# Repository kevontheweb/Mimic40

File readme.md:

# Mimic40

A tiny ortho board that is pretending to be a fullsize. 

> I have not ordered any pcbs yet so consider these files *under development* until i can order some to test if they work.

<!--  -->

## tools used to build

1. [KLE](http://www.keyboard-layout-editor.com/##@_name=Mimic40&author=kevontheweb.net&background_name=PBT%20Black&style=background-image%2F:%20url('%2F%2Fbg%2F%2Fplastic%2F%2Fpbt-black.png')%2F%3B&$$hashKey=0BG%3B&radii=10px&switchMount=cherry&switchBrand=gateron&switchType=KS-3-Yellow&pcb:false&plate:true%3B&@_c=%23ffffff&p=DSA&f:4%3B&=Tab&=Q&=W&=E&=R&=T&=Y&=U&=I&=O&=P&=Back%20Space&=Delete&_x:0.5%3B&=1&=2&=3%3B&@_c=%23c7c7c7%3B&=Esc&_c=%23ffffff%3B&=A&=S&=D&_n:true%3B&=F&=G&=H&_n:true%3B&=J&=K&=L&=%2F%3B&='&=Return&_x:0.5%3B&=4&=5&=6%3B&@=Shift&=Z&=X&=C&=V&=B&=N&=M&=,&=.&=%2F%2F&=Shift&_x:1.5%3B&=7&=8&=9%3B&@_y:-0.75&x:12.25&t=%23ffffff%3B&=%2F&uarr%2F%3B%3B&@_y:-0.25&t=%23000000&w:1.25%3B&=Ctrl&_w:1.25%3B&=Alt&_w:1.25%3B&=Super&_t=%23ffffff&w:1.25%3B&=%2F&dArr%2F%3B&_t=%23000000&a:7&w:2%3B&=&_t=%23ffffff&a:4&w:1.25%3B&=%2F&uArr%2F%3B&_t=%23000000&w:1.25%3B&=Alt&_w:1.25%3B&=Fn&_x:3.75%3B&=0&=Enter%3B&@_y:-0.75&x:11.25&t=%23ffffff%3B&=%2F&larr%2F%3B&=%2F&darr%2F%3B&=%2F&rarr%2F)
2. [kicad](https://www.kicad.org/download/) EDA
5. [cherry mx datasheet](https://imgur.com/a/XMoHF)
<!-- x. [keyboard firmware builder](https://builder.mrkeebs.com/) for the matrix (if handwired) -->

These may be helpful for future in the design of a case

1. [builder.swillkb](builder.swillkb.com/) for the case
2. [ai03 plate generator](https://kbplate.ai03.com/)

## screenshots

## references

> this was in part inspired by  [This reddit post](https://www.reddit.com/r/MechanicalKeyboards/comments/ksto32/chocolate_bar/?utm_source=share&utm_medium=web2x&context=3).

# to do

- [x] define outer geometry
- [x] per key rgb
- [x] route rows and columns
- [x] switch to rp2040 based design (no dev board)
- [x] make plate cutout file (remember to add a 2u plate mount stabiliser)
- [ ] design a case (acrlic laser cut or possible 3d printed)
- [ ] order pcbs to test
- [ ] firmware
- [ ] take it from there

## how to order

- upload gerbers
- upload bom and pos files
- confirm placements
- order missing parts elsewhere (F1 and the sockets)

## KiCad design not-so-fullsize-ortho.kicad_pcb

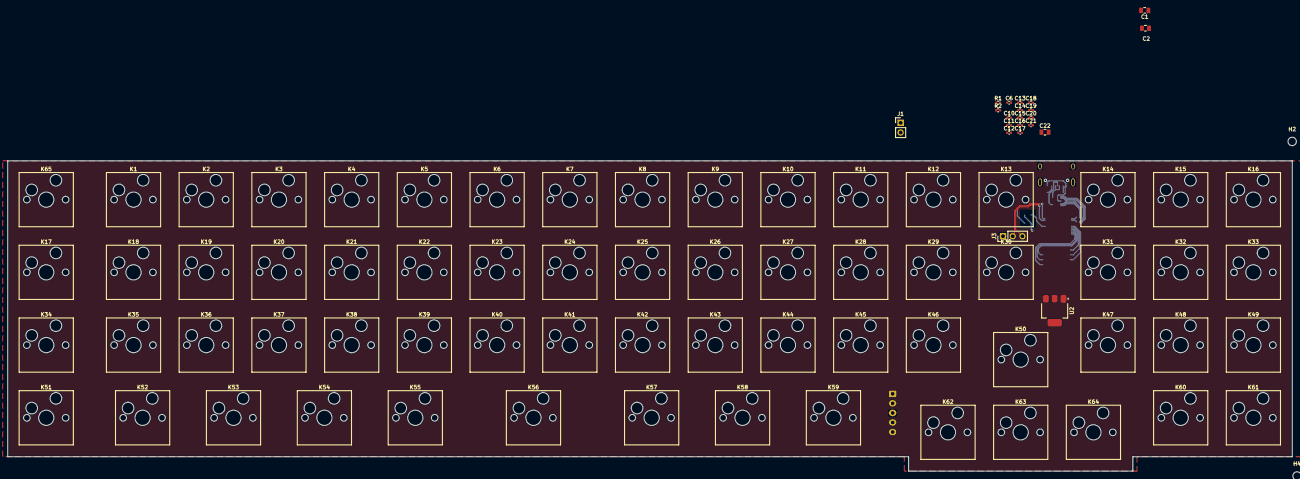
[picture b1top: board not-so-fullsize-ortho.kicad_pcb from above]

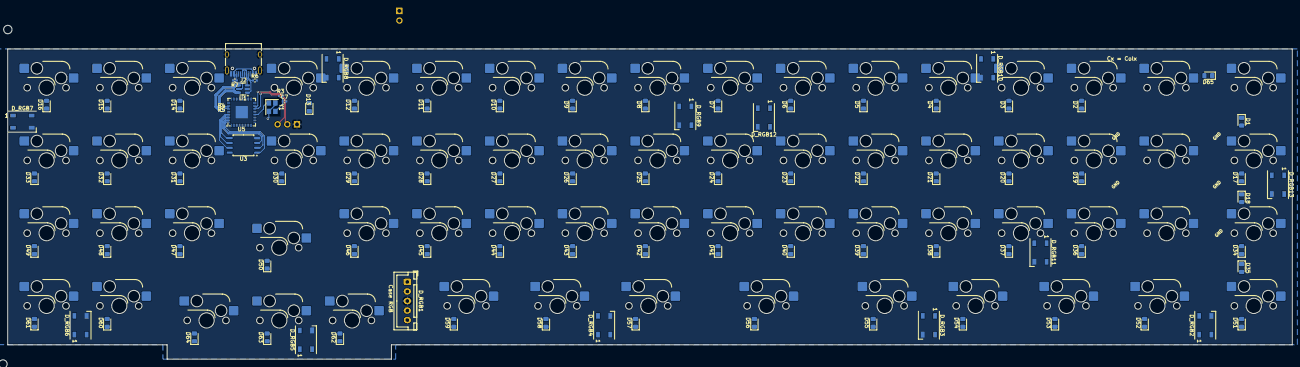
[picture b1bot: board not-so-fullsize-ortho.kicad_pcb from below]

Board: 2 copper layers, 336.5 x 81.2 mm, 179 parts (89 on the bottom side), 122 nets.

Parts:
C1, C2, C22: 10u; C_0805_2012Metric
C6, C7: 15p; C_0402_1005Metric
C10, C11, C12, C14, C16, C17, C18, C19, C20, C21: 100n; C_0402_1005Metric
C13, C15: 1u; C_0402_1005Metric
D1, D2, D3, D4, D5, D6, D7, D8, D9, D10, D11, D12, D13, D14, D15, D16, D17, D18, D19, D20, D21, D22, D23, D24, D25, D26, D27, D28, D29, D30, D31, D32, D33, D34, D35, D36, D37, D38, D39, D40, D41, D42, D43, D44, D45, D46, D47, D48, D49, D50, D51, D52, D53, D54, D55, D56, D57, D58, D59, D60, D61, D62, D63, D64, D65: D; D_0805_2012Metric_Pad1.15x1.40mm_HandSolder
D_RGB1: WS2812B; JST_XH_B5B-XH-A_1x05_P2.50mm_Vertical
D_RGB2, D_RGB3, D_RGB4, D_RGB5, D_RGB6, D_RGB7, D_RGB8, D_RGB9, D_RGB10, D_RGB11, D_RGB12, D_RGB13: WS2812B; LED_WS2812B_PLCC4_5.0x5.0mm_P3.2mm
H1, H2, H3, H4: MountingHole; MountingHole_2.2mm_M2
J1: Conn_01x02; PinHeader_1x02_P2.54mm_Vertical
J2: USB_C_Receptacle_USB2.0_16P; USB_C_Receptacle_HRO_TYPE-C-31-M-12
J3: Conn_01x03; PinHeader_1x03_P2.54mm_Vertical
K1: Home; SW_Hotswap_Kailh_MX_1.00u
K2: End; SW_Hotswap_Kailh_MX_1.00u
K3: Vol +; SW_Hotswap_Kailh_MX_1.00u
K4: Vol -; SW_Hotswap_Kailh_MX_1.00u
K5: Tab; SW_Hotswap_Kailh_MX_1.00u
K6: Esc; SW_Hotswap_Kailh_MX_1.00u
K7, K48: Shift; SW_Hotswap_Kailh_MX_1.00u
K8: Ctrl; SW_Hotswap_Kailh_MX_1.00u
K9: Q; SW_Hotswap_Kailh_MX_1.00u
K10: A; SW_Hotswap_Kailh_MX_1.00u
K11: Z; SW_Hotswap_Kailh_MX_1.00u
K12, K38: Alt; SW_Hotswap_Kailh_MX_1.00u
K13: W; SW_Hotswap_Kailh_MX_1.00u
K14: S; SW_Hotswap_Kailh_MX_1.00u
K15: X; SW_Hotswap_Kailh_MX_1.00u
K16: Super; SW_Hotswap_Kailh_MX_1.00u
K17: E; SW_Hotswap_Kailh_MX_1.00u
K18: D; SW_Hotswap_Kailh_MX_1.00u
K19: C; SW_Hotswap_Kailh_MX_1.00u
K20: &dArr;; SW_Hotswap_Kailh_MX_1.00u
K21: R; SW_Hotswap_Kailh_MX_1.00u
K22: F; SW_Hotswap_Kailh_MX_1.00u
K23: V; SW_Hotswap_Kailh_MX_1.00u
K24: T; SW_Hotswap_Kailh_MX_1.00u
K25: G; SW_Hotswap_Kailh_MX_1.00u
K26: B; SW_Hotswap_Kailh_MX_1.00u
K27: Blank; SW_Hotswap_Kailh_MX_1.00u
K28: Y; SW_Hotswap_Kailh_MX_1.00u
K29: H; SW_Hotswap_Kailh_MX_1.00u
K30: N; SW_Hotswap_Kailh_MX_1.00u
K31: U; SW_Hotswap_Kailh_MX_1.00u
K32: J; SW_Hotswap_Kailh_MX_1.00u
K33: M; SW_Hotswap_Kailh_MX_1.00u
K34: &uArr;; SW_Hotswap_Kailh_MX_1.00u
K35: I; SW_Hotswap_Kailh_MX_1.00u
K36: K; SW_Hotswap_Kailh_MX_1.00u
K37: ,; SW_Hotswap_Kailh_MX_1.00u
K39: O; SW_Hotswap_Kailh_MX_1.00u
K40: L; SW_Hotswap_Kailh_MX_1.00u
K41: .; SW_Hotswap_Kailh_MX_1.00u
K42: Fn; SW_Hotswap_Kailh_MX_1.00u
K43: P; SW_Hotswap_Kailh_MX_1.00u
K44: ;; SW_Hotswap_Kailh_MX_1.00u
K45: /; SW_Hotswap_Kailh_MX_1.00u
K46: Back Space; SW_Hotswap_Kailh_MX_1.00u
K47: '; SW_Hotswap_Kailh_MX_1.00u
K49: &larr;; SW_Hotswap_Kailh_MX_1.00u
K50: Delete; SW_Hotswap_Kailh_MX_1.00u
K51: Return; SW_Hotswap_Kailh_MX_1.00u
K52: &uarr;; SW_Hotswap_Kailh_MX_1.00u
K53: &darr;; SW_Hotswap_Kailh_MX_1.00u
K54: &rarr;; SW_Hotswap_Kailh_MX_1.00u
K55: 1; SW_Hotswap_Kailh_MX_1.00u
K56: 4; SW_Hotswap_Kailh_MX_1.00u
K57: 7; SW_Hotswap_Kailh_MX_1.00u
K58: 2; SW_Hotswap_Kailh_MX_1.00u
K59: 5; SW_Hotswap_Kailh_MX_1.00u
K60: 8; SW_Hotswap_Kailh_MX_1.00u
K61: 0; SW_Hotswap_Kailh_MX_1.00u
K62: 3; SW_Hotswap_Kailh_MX_1.00u
K63: 6; SW_Hotswap_Kailh_MX_1.00u
K64: 9; SW_Hotswap_Kailh_MX_1.00u
K65: Enter; SW_Hotswap_Kailh_MX_1.00u
R1, R3: 1k; R_0402_1005Metric
R2: DNF; R_0402_1005Metric
R4, R5: 27; R_0402_1005Metric
R6, R7: 5.1k; R_0402_1005Metric
U1: USBLC6-2SC6; SOT-23-6
U2: NCP1117-3.3_SOT223; SOT-223-3_TabPin2
U3: W25Q128JVS; SOIC-8_5.23x5.23mm_P1.27mm
U5: RP2040; QFN-56-1EP_7x7mm_P0.4mm_EP3.2x3.2mm
Y1: ABM8-272-T3; Crystal_SMD_3225-4Pin_3.2x2.5mm

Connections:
+1V1: C11.1, C12.1, C13.1, U5.23 (DVDD), U5.45 (VREG_VOUT), U5.50 (DVDD)
+3V3: C2.1, C10.1, C14.1, C15.1, C16.1, C17.1, C18.1, C19.1, C20.1, C21.1, C22.1, R2.1, U2.2 (VO), U3.8 (VCC), U5.1 (IOVDD), U5.10 (IOVDD), U5.22 (IOVDD), U5.33 (IOVDD), U5.42 (IOVDD), U5.43 (ADC_AVDD), U5.44 (VREG_IN), U5.48 (USB_VDD), U5.49 (IOVDD)
/Col_0: K1.1, K2.1, K3.1, K4.1, U5.2 (GPIO0)
/Col_1: K5.1, K6.1, K7.1, K8.1, U5.3 (GPIO1)
/Col_2: K9.1, K10.1, K11.1, K12.1, U5.4 (GPIO2)
/Col_3: K13.1, K14.1, K15.1, U5.18 (GPIO15)
/Col_4: K16.1, K17.1, K18.1, K19.1, U5.17 (GPIO14)
/Col_5: K20.1, K21.1, K22.1, K23.1, U5.15 (GPIO12)
/Col_6: K24.1, K25.1, K26.1, K27.1, U5.14 (GPIO11)
/Col_7: K28.1, K29.1, K30.1, U5.13 (GPIO10)
/Col_8: K31.1, K32.1, K33.1, K34.1, U5.12 (GPIO9)
/Col_9: K35.1, K36.1, K37.1, K38.1, U5.11 (GPIO8)
/Col_10: K39.1, K40.1, K41.1, K42.1, U5.9 (GPIO7)
/Col_11: K43.1, K44.1, K45.1, U5.8 (GPIO6)
/Col_12: K46.1, K47.1, K48.1, K49.1, U5.7 (GPIO5)
/Col_13: K50.1, K51.1, K52.1, K53.1, U5.16 (GPIO13)
/Col_14: K54.1, K55.1, K56.1, K57.1, U5.6 (GPIO4)
/Col_15: K58.1, K59.1, K60.1, K61.1, U5.5 (GPIO3)
/Col_16: K62.1, K63.1, K64.1, K65.1, U5.27 (GPIO16)
/RP2040/QSPI_SCLK: U3.6 (CLK), U5.52 (QSPI_SCLK)
/RP2040/QSPI_SD0: U3.5 (DI(IO0)), U5.53 (QSPI_SD0)
/RP2040/QSPI_SD1: U3.2 (DO(IO1)), U5.55 (QSPI_SD1)
/RP2040/QSPI_SD2: U3.3 (IO2), U5.54 (QSPI_SD2)
/RP2040/QSPI_SD3: U3.7 (IO3), U5.51 (QSPI_SD3)
/RP2040/QSPI_SS: R1.1, R2.2, U3.1 (~CS), U5.56 (QSPI_SS)
/RP2040/XIN: C6.1, U5.20 (XIN), Y1.1
/RP2040/XOUT: R3.1, U5.21 (XOUT)
/RP2040/~USB_BOOT: J1.1, R1.2
/Row_0: D1.1 (K), D5.1 (K), D9.1 (K), D13.1 (K), D17.1 (K), D21.1 (K), D24.1 (K), D28.1 (K), D31.1 (K), D35.1 (K), D39.1 (K), D43.1 (K), D46.1 (K), D50.1 (K), D55.1 (K), D58.1 (K), D62.1 (K), U5.32 (GPIO21)
/Row_1: D2.1 (K), D6.1 (K), D10.1 (K), D14.1 (K), D18.1 (K), D22.1 (K), D25.1 (K), D29.1 (K), D32.1 (K), D36.1 (K), D40.1 (K), D44.1 (K), D47.1 (K), D51.1 (K), D56.1 (K), D59.1 (K), D63.1 (K), U5.31 (GPIO20)
/Row_2: D3.1 (K), D7.1 (K), D11.1 (K), D15.1 (K), D19.1 (K), D23.1 (K), D26.1 (K), D30.1 (K), D33.1 (K), D37.1 (K), D41.1 (K), D45.1 (K), D48.1 (K), D52.1 (K), D57.1 (K), D60.1 (K), D64.1 (K), U5.30 (GPIO19)
/Row_3: D4.1 (K), D8.1 (K), D12.1 (K), D16.1 (K), D20.1 (K), D27.1 (K), D34.1 (K), D38.1 (K), D42.1 (K), D49.1 (K), D53.1 (K), D54.1 (K), D61.1 (K), D65.1 (K), U5.29 (GPIO18)
/SWCLK: J3.3, U5.24 (SWCLK)
/SWD: J3.2, U5.25 (SWD)
/USB/D+: J2.A6 (D+), J2.B6 (D+), U1.3 (I/O2)
/USB/D-: J2.A7 (D-), J2.B7 (D-), U1.1 (I/O1)
/USB_D+: R4.1, U1.4 (I/O2)
/USB_D-: R5.2, U1.6 (I/O1)
GND: C1.2, C2.2, C6.2, C7.2, C10.2, C11.2, C12.2, C13.2, C14.2, C15.2, C16.2, C17.2, C18.2, C19.2, C20.2, C21.2, C22.2, D_RGB1.3 (VSS), D_RGB2.3 (VSS), D_RGB3.3 (VSS), D_RGB4.3 (VSS), D_RGB5.3 (VSS), D_RGB6.3 (VSS), D_RGB7.3 (VSS), D_RGB8.3 (VSS), D_RGB9.3 (VSS), D_RGB10.3 (VSS), D_RGB11.3 (VSS), D_RGB12.3 (VSS), D_RGB13.3 (VSS), J1.2, J2.A1 (GND), J2.A12 (GND), J2.B1 (GND), J2.B12 (GND), J2.S1 (SHIELD), J3.1, R6.2, R7.2, U1.2 (GND), U2.1 (GND), U3.4 (GND), U5.57 (GND), Y1.2, Y1.4
unnamed: C7.1, R3.2, Y1.3
unnamed: D1.2 (A), K1.2
unnamed: D2.2 (A), K2.2
unnamed: D3.2 (A), K3.2
unnamed: D4.2 (A), K4.2
unnamed: D5.2 (A), K5.2
unnamed: D6.2 (A), K6.2
unnamed: D7.2 (A), K7.2
unnamed: D8.2 (A), K8.2
unnamed: D9.2 (A), K9.2
unnamed: D10.2 (A), K10.2
unnamed: D11.2 (A), K11.2
unnamed: D12.2 (A), K12.2
unnamed: D13.2 (A), K13.2
unnamed: D14.2 (A), K14.2
unnamed: D15.2 (A), K15.2
unnamed: D16.2 (A), K16.2
unnamed: D17.2 (A), K17.2
unnamed: D18.2 (A), K18.2
unnamed: D19.2 (A), K19.2
unnamed: D20.2 (A), K20.2
unnamed: D21.2 (A), K21.2
unnamed: D22.2 (A), K22.2
unnamed: D23.2 (A), K23.2
unnamed: D24.2 (A), K24.2
unnamed: D25.2 (A), K25.2
unnamed: D26.2 (A), K26.2
unnamed: D27.2 (A), K27.2
unnamed: D28.2 (A), K28.2
unnamed: D29.2 (A), K29.2
unnamed: D30.2 (A), K30.2
unnamed: D31.2 (A), K31.2
unnamed: D32.2 (A), K32.2
unnamed: D33.2 (A), K33.2
unnamed: D34.2 (A), K34.2
unnamed: D35.2 (A), K35.2
unnamed: D36.2 (A), K36.2
unnamed: D37.2 (A), K37.2
unnamed: D38.2 (A), K38.2
unnamed: D39.2 (A), K39.2
unnamed: D40.2 (A), K40.2
unnamed: D41.2 (A), K41.2
unnamed: D42.2 (A), K42.2
unnamed: D43.2 (A), K43.2
unnamed: D44.2 (A), K44.2
unnamed: D45.2 (A), K45.2
unnamed: D46.2 (A), K46.2
unnamed: D47.2 (A), K47.2
unnamed: D48.2 (A), K48.2
unnamed: D49.2 (A), K49.2
unnamed: D50.2 (A), K50.2
unnamed: D51.2 (A), K51.2
unnamed: D52.2 (A), K52.2
unnamed: D53.2 (A), K53.2
unnamed: D54.2 (A), K54.2
unnamed: D55.2 (A), K55.2
unnamed: D56.2 (A), K56.2
unnamed: D57.2 (A), K57.2
unnamed: D58.2 (A), K58.2
unnamed: D59.2 (A), K59.2
unnamed: D60.2 (A), K60.2
unnamed: D61.2 (A), K61.2
unnamed: D62.2 (A), K62.2
unnamed: D63.2 (A), K63.2
unnamed: D64.2 (A), K64.2
unnamed: D65.2 (A), K65.2
unnamed: D_RGB1.2 (DOUT), D_RGB4.4 (DIN)
unnamed: D_RGB2.2 (DOUT), D_RGB5.4 (DIN)
unnamed: D_RGB3.2 (DOUT), D_RGB6.4 (DIN)
unnamed: D_RGB4.2 (DOUT), D_RGB7.4 (DIN)
unnamed: D_RGB6.2 (DOUT), D_RGB8.4 (DIN)
unnamed: D_RGB7.2 (DOUT), D_RGB9.4 (DIN)
unnamed: D_RGB8.2 (DOUT), D_RGB10.4 (DIN)
unnamed: D_RGB10.2 (DOUT), D_RGB12.4 (DIN)
unnamed: D_RGB9.2 (DOUT), D_RGB11.4 (DIN)
unnamed: D_RGB11.2 (DOUT), D_RGB13.4 (DIN)
unnamed: D_RGB2.4 (DIN), D_RGB12.2 (DOUT)
unnamed: D_RGB3.4 (DIN), D_RGB13.2 (DOUT)
unnamed: J2.A5 (CC1), R6.1
unnamed: J2.B5 (CC2), R7.1
unnamed: R5.1, U5.46 (USB_DM)
unnamed: R4.2, U5.47 (USB_DP)
VBUS: C1.1, D_RGB1.1 (VDD), D_RGB2.1 (VDD), D_RGB3.1 (VDD), D_RGB4.1 (VDD), D_RGB5.1 (VDD), D_RGB6.1 (VDD), D_RGB7.1 (VDD), D_RGB8.1 (VDD), D_RGB9.1 (VDD), D_RGB10.1 (VDD), D_RGB11.1 (VDD), D_RGB12.1 (VDD), D_RGB13.1 (VDD), J2.A4 (VBUS), J2.A9 (VBUS), J2.B4 (VBUS), J2.B9 (VBUS), U1.5 (VBUS), U2.3 (VI)

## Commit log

2023-02-14 add production files (gerbers and such) for JLC PCB
2024-08-07 rework for rp2040 (not pico dev board)
    kicad 8 version bump, much better schematic, some DRC rules, start with layout of rp2040/USB portion of board, will need to reroute all the rows/cols when done.
2024-08-08 layout rp2040 mwe
2024-08-11 per key rgb (reverse mount sk6812 mini e, geometry finalisation
2024-08-12 remove left most column, reroute rp2040
    remove left most column, reroute rp2040 to fit in-between switches, no more oled, last 2 cols (right) are snap off.
    still to do:
    - check that the snap cutouts aren't too much,
    - add mounting holes for if the side is snapped off.
    - still to route columns/rows
2024-08-17 gitignore
2024-08-17 routing, rotate leds to make tracks easier
2024-08-18 pretty much done
2024-08-19 test prod files for jlc quote, wrong diode footprint 🤦‍
2024-08-22 sod-128 diodes, still wrong it was supposed to be 123
2024-08-22 rename, pcbway prod
2024-08-22 branding
2024-08-22 prod files, fix silkscreens
2024-08-22 last before prod
2024-08-26 plate + usb soldermask fix
2024-08-26 reame
2024-08-26 pcbway bom
2024-08-26 add part nums for bom
2024-08-26 finishing touches b4 prod
2024-08-31 cleanup, fix soldermask expansion and silkscreens, boms for jlc and pcbway
2024-08-31 udpate plate
2024-09-22 usb changes for high power (leds)
2024-10-06 bulk cap and level shifter (still need to lay out)
2024-10-06 clean
2024-10-08 bulk caps for power (todo, split 470uF cap so that it can be shorter)
2024-10-10 add debug led, make bulk caps smaller, export plate and bottom for rudimentary case
2024-10-12 enlarge mounting holes, custom rules
2024-10-19 fab output changes (part choice updates)
2024-11-12 switch to solderable sockets, you can millmax if you want.
